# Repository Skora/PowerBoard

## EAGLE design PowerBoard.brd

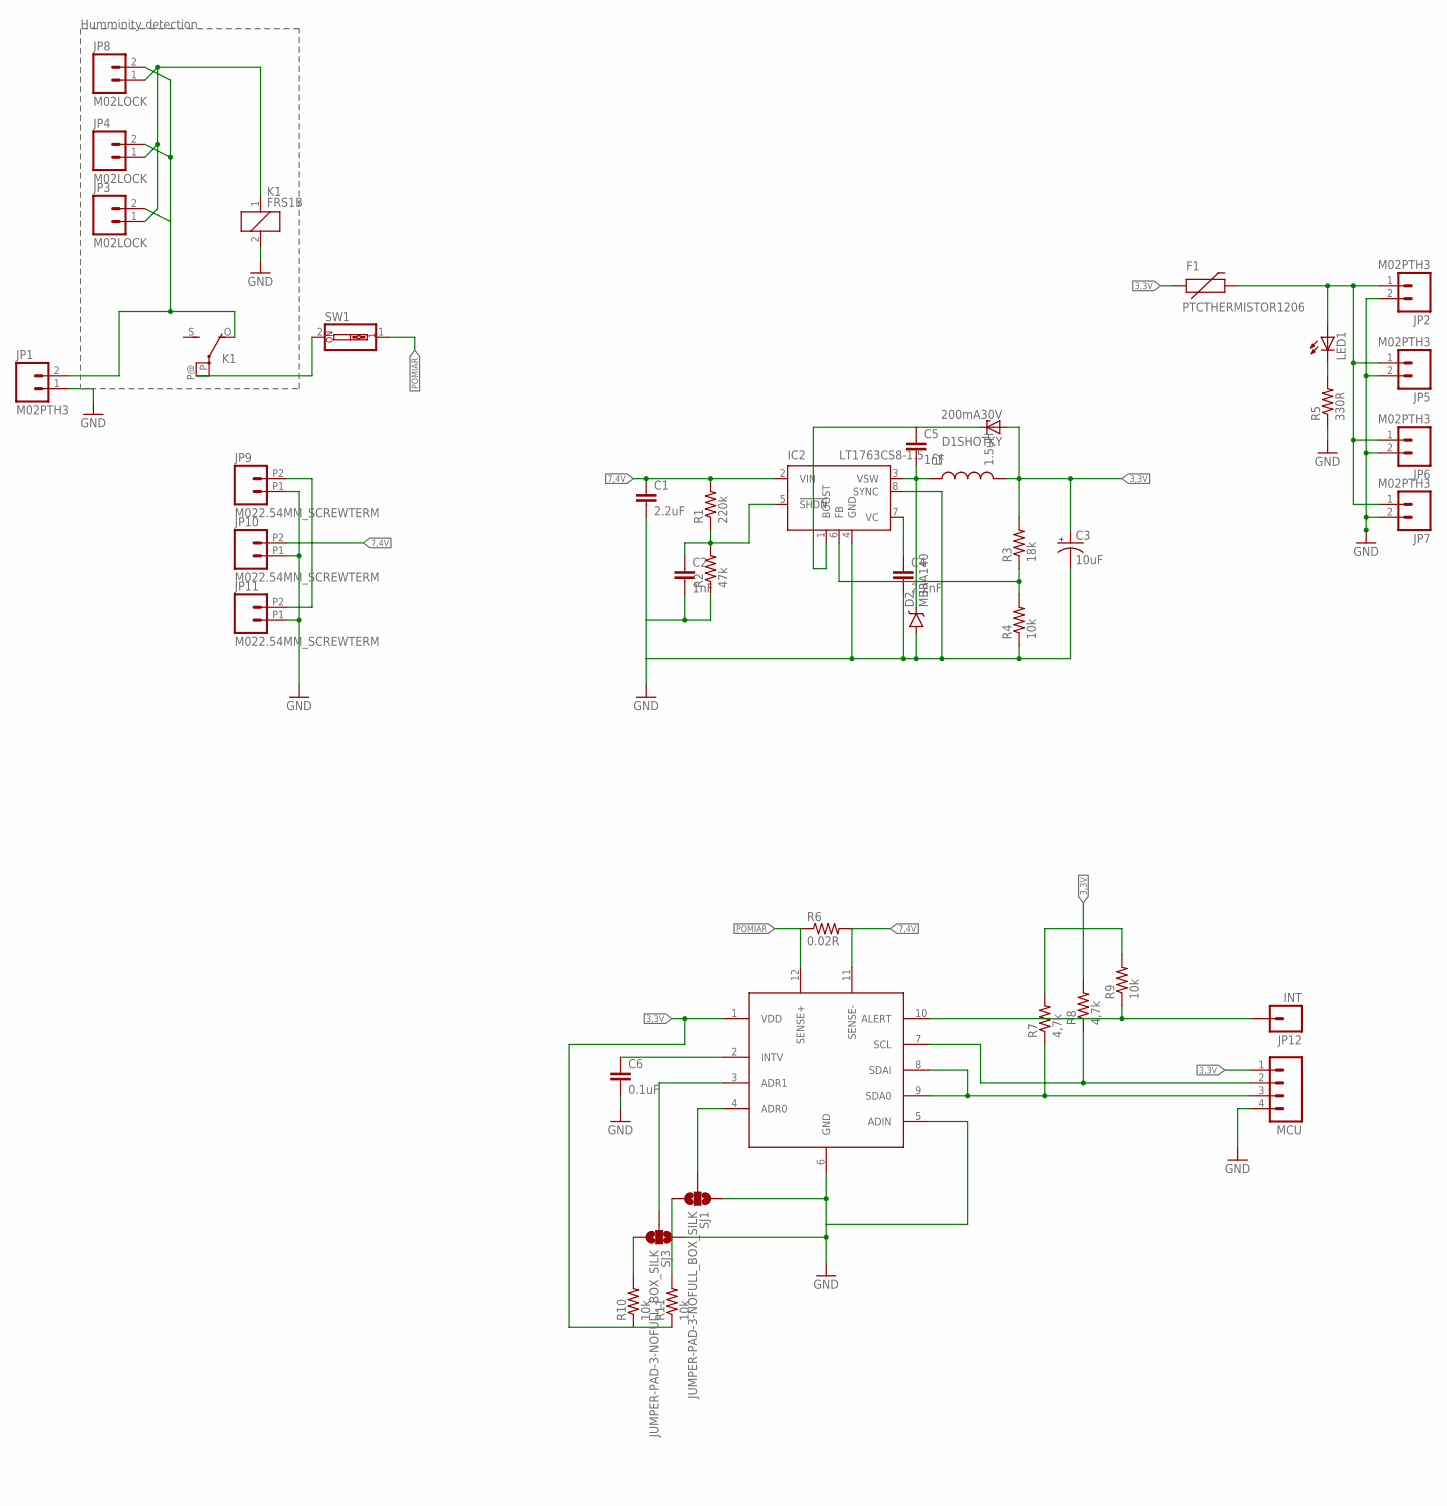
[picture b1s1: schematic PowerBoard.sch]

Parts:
C1: 2.2uF; 0805
C2, C5: 1nF; 0805
C3: 10uF; PANASONIC_C
C4: 2.2nF; 0805
C6: 0.1uF; 0805
D1SHOTKY: 200mA30V; SOD80C
D2: MBRA140; SMA-DIODE
F1: PTCTHERMISTOR1206; PTC-1206
IC2: LT1763CS8-1.5; SOIC8
JP1, JP2, JP5, JP6, JP7: M02PTH3; 1X02_LONGPADS
JP3, JP4, JP8: M02LOCK; 1X02_LOCK
JP9, JP10, JP11: M022.54MM_SCREWTERM; 1X02_2.54_SCREWTERM
JP12: INT; 1X01_LONGPAD
K1: FRS1B
L2: 1.5uH; B82462G
LED1: LEDSML0805; SML0805
MCU: M04POLAR_LOCK; MOLEX-1X4_LOCK
R1: 220k; 0805
R2: 47k; 0805
R3: 18k; 0805
R4, R9, R10, R11: 10k; 0805
R5: 330R; 0805
R6: 0.02R; R2512
R7, R8: 4,7k; 0805
SJ1, SJ3: JUMPER-PAD-3-NOFULL_BOX_SILK; PAD-JUMPER-3-NO_YES_SILK_FULL_BOX
SW1: SW_DIP-1; EDG-01
U$1: LTC2945; SOP65P490X110-12N

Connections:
3,3V: C3.+, D1SHOTKY.A, F1.1, L2.P$2 (2), MCU.1, R3.2, R7.2, R8.2, R9.2, R10.1, R11.1, U$1.1 (VDD)
7,4V: C1.1, IC2.2 (VIN), JP9.P2 (2), JP10.P2 (2), JP11.P2 (2), R1.2, R6.2, U$1.11 (SENSE-)
AFERFUSE: F1.2, JP2.1, JP5.1, JP6.1, JP7.1, LED1.A
COIL: JP3.1, JP4.1, JP8.1, K1.1
COUT: C5.2, D2.C, IC2.3 (VSW), L2.P$1 (1)
GND: C1.2, C2.2, C3.-, C4.2, C6.2, D2.A, IC2.4 (GND), IC2.8 (SYNC), JP1.1, JP2.2, JP5.2, JP6.2, JP7.2, JP9.P1 (1), JP10.P1 (1), JP11.P1 (1), K1.2, MCU.4, R2.1, R4.1, R5.1, SJ1.1, SJ3.1, U$1.5 (ADIN), U$1.6 (GND)
unnamed: C2.1, IC2.5 (!SHDN), R1.1, R2.2
unnamed: IC2.6 (FB), R3.1, R4.2
unnamed: C4.1, IC2.7 (VC)
unnamed: C5.1, D1SHOTKY.C, IC2.1 (BOOST)
unnamed: LED1.C, R5.2
unnamed: JP12.1, R9.1, U$1.10 (ALERT)
unnamed: MCU.2, R8.1, U$1.7 (SCL)
unnamed: MCU.3, R7.1, U$1.8 (SDAI), U$1.9 (SDA0)
unnamed: C6.1, U$1.2 (INTV)
unnamed: SJ3.2, U$1.3 (ADR1)
unnamed: SJ1.2, U$1.4 (ADR0)
unnamed: R10.2, SJ3.3
unnamed: R11.2, SJ1.3
POMIAR: R6.1, SW1.1, U$1.12 (SENSE+)
PRERELAY: JP1.2, JP3.2, JP4.2, JP8.2, K1.O
PRESWITCH: K1.P, K1.P@, SW1.2

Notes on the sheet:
Humminity detection

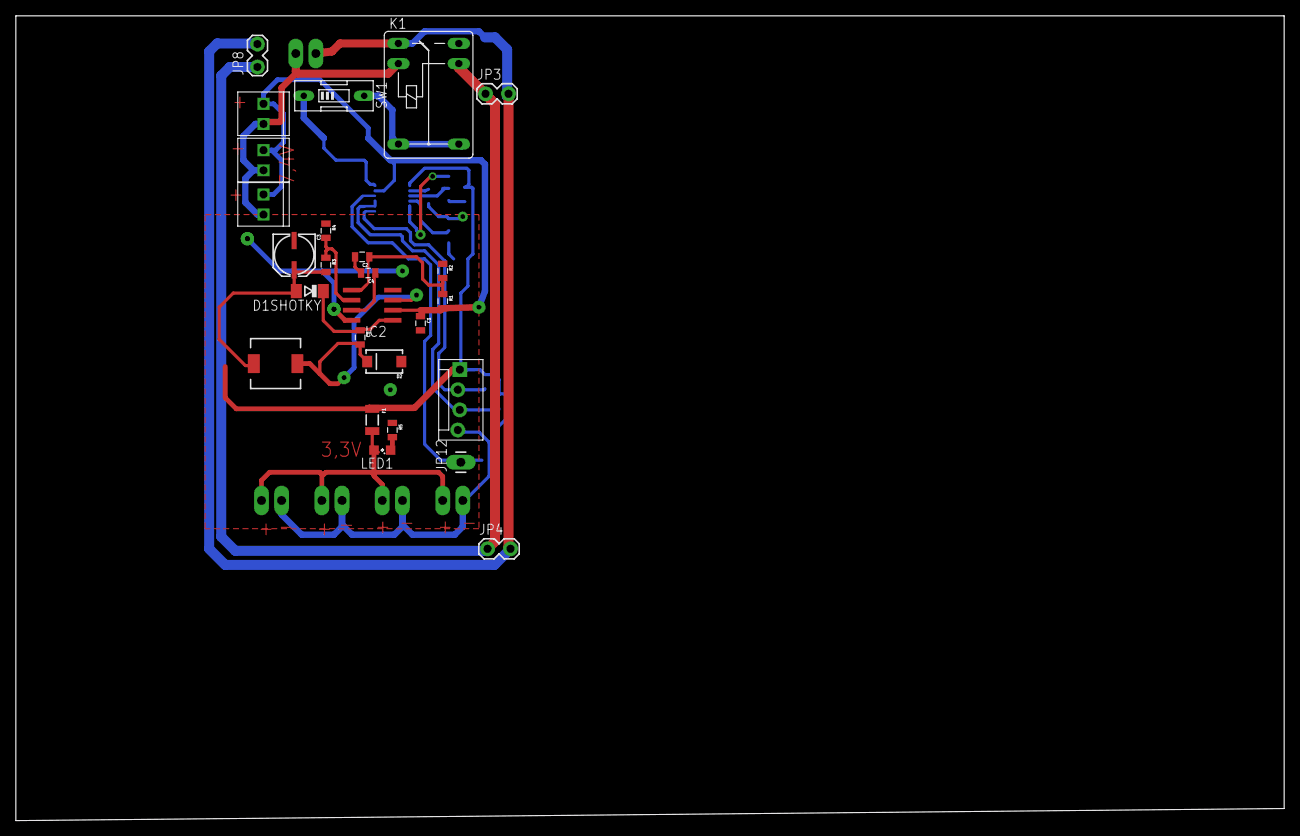
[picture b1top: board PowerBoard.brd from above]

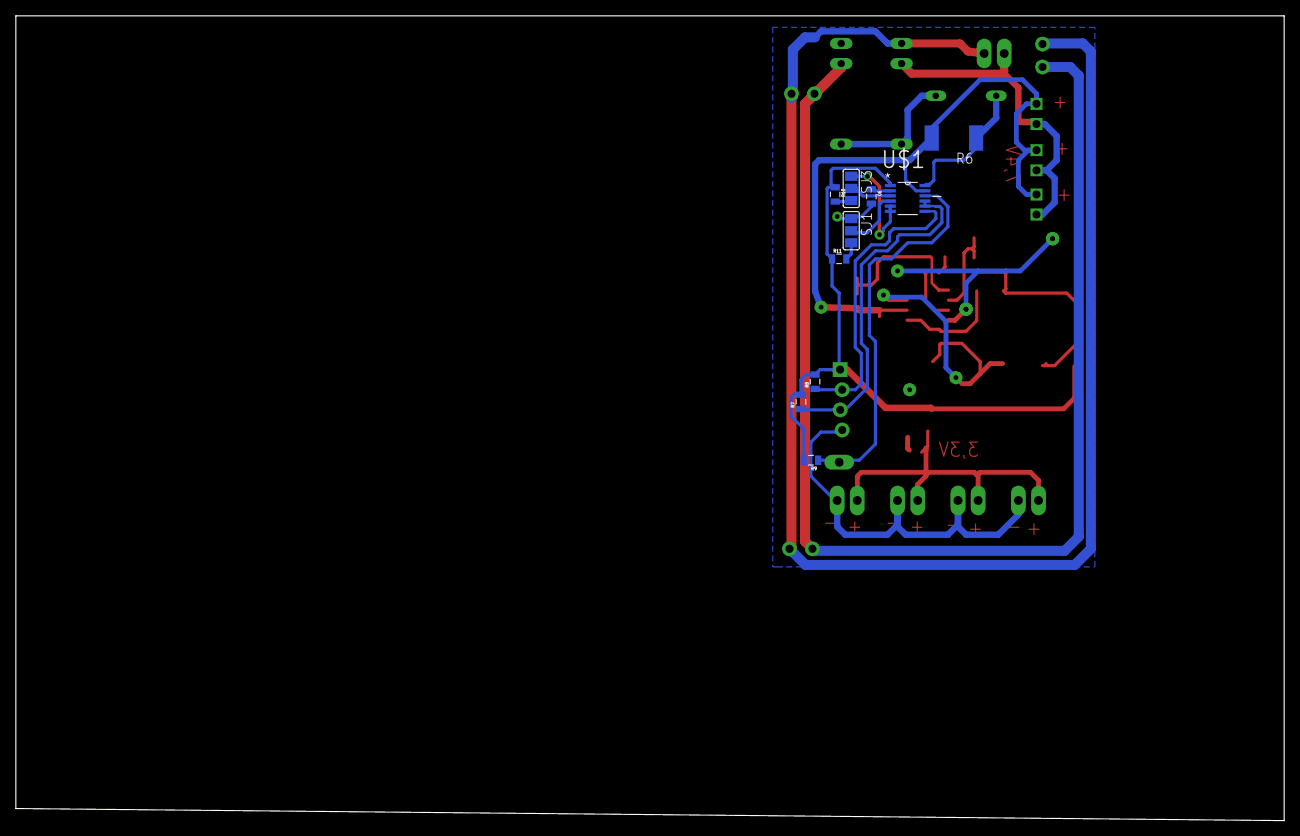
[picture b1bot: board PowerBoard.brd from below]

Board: 2 copper layers, 160.0 x 101.5 mm, 41 parts (10 on the bottom side), 22 nets.

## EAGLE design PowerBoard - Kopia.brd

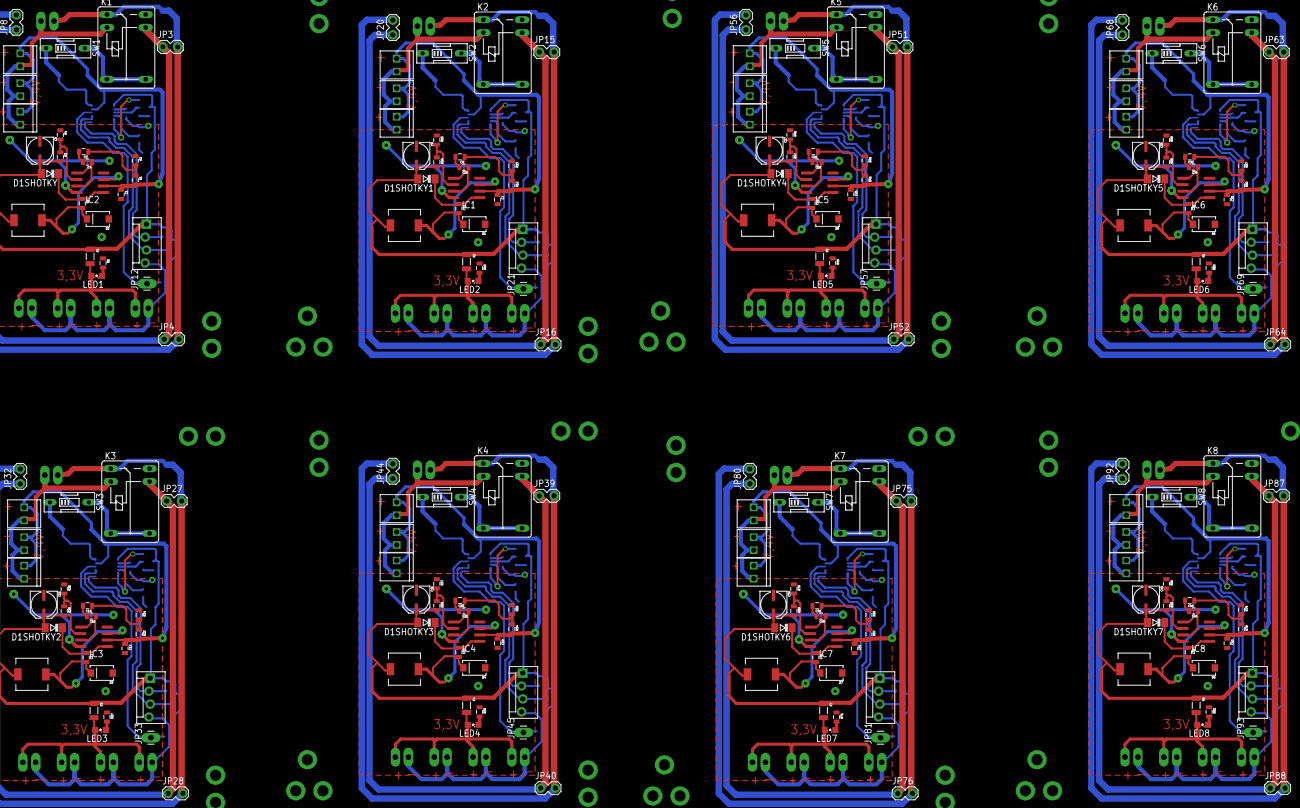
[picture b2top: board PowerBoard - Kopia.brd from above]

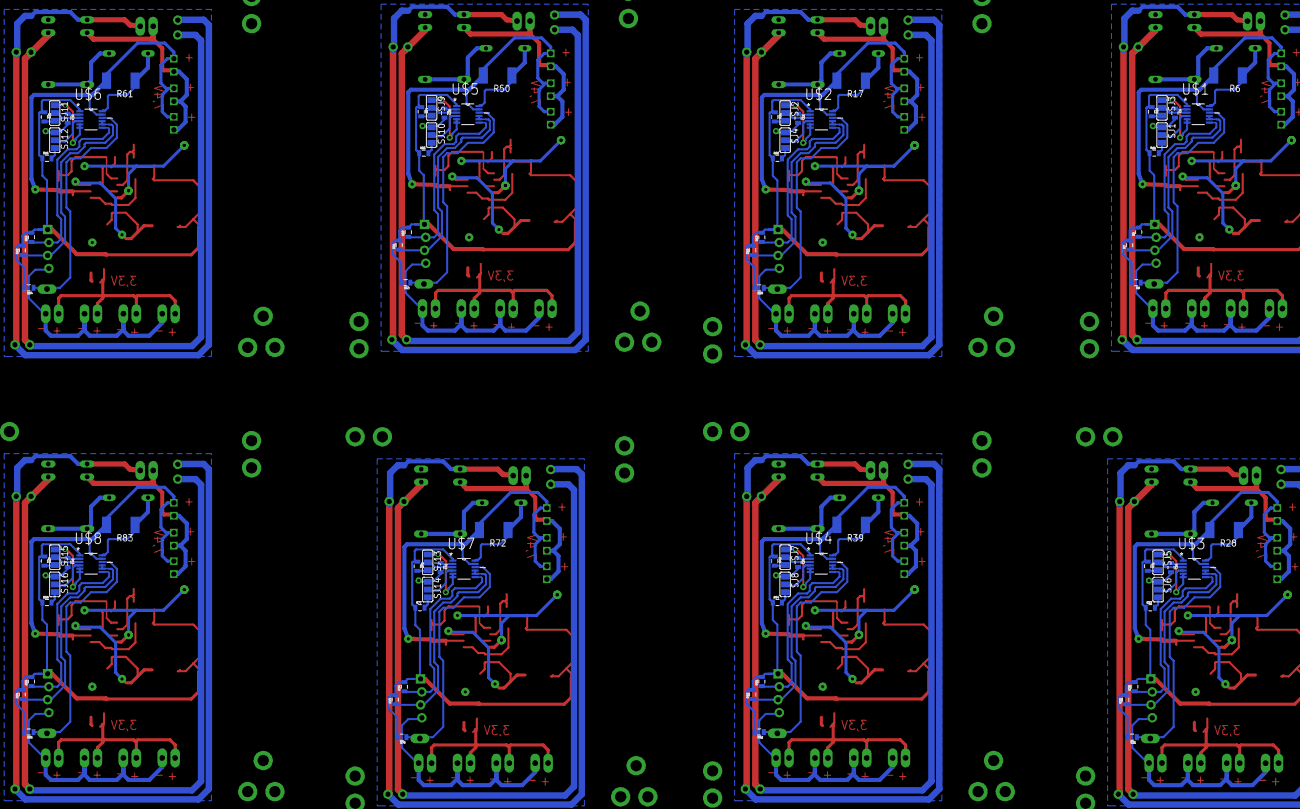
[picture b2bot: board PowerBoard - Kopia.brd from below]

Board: 2 copper layers, 328 parts (80 on the bottom side), 176 nets.

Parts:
C1, C7, C13, C19, C25, C31, C37, C43: 2.2uF; 0805
C2, C5, C8, C11, C14, C17, C20, C23, C26, C29, C32, C35, C38, C41, C44, C47: 1nF; 0805
C3, C9, C15, C21, C27, C33, C39, C45: 10uF; PANASONIC_C
C4, C10, C16, C22, C28, C34, C40, C46: 2.2nF; 0805
C6, C12, C18, C24, C30, C36, C42, C48: 0.1uF; 0805
D1, D2, D3, D4, D5, D6, D7, D8: MBRA140; SMA-DIODE
D1SHOTKY, D1SHOTKY1, D1SHOTKY2, D1SHOTKY3, D1SHOTKY4, D1SHOTKY5, D1SHOTKY6, D1SHOTKY7: 200mA30V; SOD80C
F1, F2, F3, F4, F5, F6, F7, F8: PTCTHERMISTOR1206; PTC-1206
IC1, IC2, IC3, IC4, IC5, IC6, IC7, IC8: LT1763CS8-1.5; SOIC8
JP1, JP2, JP5, JP6, JP7, JP13, JP14, JP17, JP18, JP19, JP25, JP26, JP29, JP30, JP31, JP37, JP38, JP41, JP42, JP43, JP49, JP50, JP53, JP54, JP55, JP61, JP62, JP65, JP66, JP67, JP73, JP74, JP77, JP78, JP79, JP85, JP86, JP89, JP90, JP91: M02PTH3; 1X02_LONGPADS
JP3, JP4, JP8, JP15, JP16, JP20, JP27, JP28, JP32, JP39, JP40, JP44, JP51, JP52, JP56, JP63, JP64, JP68, JP75, JP76, JP80, JP87, JP88, JP92: M02LOCK; 1X02_LOCK
JP9, JP10, JP11, JP22, JP23, JP24, JP34, JP35, JP36, JP46, JP47, JP48, JP58, JP59, JP60, JP70, JP71, JP72, JP82, JP83, JP84, JP94, JP95, JP96: M022.54MM_SCREWTERM; 1X02_2.54_SCREWTERM
JP12, JP21, JP33, JP45, JP57, JP69, JP81, JP93: INT; 1X01_LONGPAD
K1, K2, K3, K4, K5, K6, K7, K8: FRS1B
L1, L2, L3, L4, L5, L6, L7, L8: 1.5uH; B82462G
LED1, LED2, LED3, LED4, LED5, LED6, LED7, LED8: SML0805
MCU, MCU1, MCU2, MCU3, MCU4, MCU5, MCU6, MCU7: MOLEX-1X4_LOCK
R1, R12, R23, R34, R45, R56, R67, R78: 220k; 0805
R2, R13, R24, R35, R46, R57, R68, R79: 47k; 0805
R3, R14, R25, R36, R47, R58, R69, R80: 18k; 0805
R4, R9, R10, R11, R15, R20, R21, R22, R26, R31, R32, R33, R37, R42, R43, R44, R48, R53, R54, R55, R59, R64, R65, R66, R70, R75, R76, R77, R81, R86, R87, R88: 10k; 0805
R5, R16, R27, R38, R49, R60, R71, R82: 330R; 0805
R6, R17, R28, R39, R50, R61, R72, R83: 0.02R; R2512
R7, R8, R18, R19, R29, R30, R40, R41, R51, R52, R62, R63, R73, R74, R84, R85: 4,7k; 0805
SJ1, SJ2, SJ3, SJ4, SJ5, SJ6, SJ7, SJ8, SJ9, SJ10, SJ11, SJ12, SJ13, SJ14, SJ15, SJ16: JUMPER-PAD-3-NOFULL_BOX_SILK; PAD-JUMPER-3-NO_YES_SILK_FULL_BOX
SW1, SW2, SW3, SW4, SW5, SW6, SW7, SW8: EDG-01
U$1, U$2, U$3, U$4, U$5, U$6, U$7, U$8: LTC2945; SOP65P490X110-12N

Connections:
3,3V: C3.+, D1SHOTKY.A, F1.1, L2.P$2, MCU.1, R3.2, R7.2, R8.2, R9.2, R10.1, R11.1, U$1.1
3,3V1: C9.+, D1SHOTKY1.A, F2.1, L1.P$2, MCU1.1, R14.2, R18.2, R19.2, R20.2, R21.1, R22.1, U$2.1
3,3V2: C15.+, D1SHOTKY2.A, F3.1, L3.P$2, MCU2.1, R25.2, R29.2, R30.2, R31.2, R32.1, R33.1, U$3.1
3,3V3: C21.+, D1SHOTKY3.A, F4.1, L4.P$2, MCU3.1, R36.2, R40.2, R41.2, R42.2, R43.1, R44.1, U$4.1
3,3V4: C27.+, D1SHOTKY4.A, F5.1, L5.P$2, MCU4.1, R47.2, R51.2, R52.2, R53.2, R54.1, R55.1, U$5.1
3,3V5: C33.+, D1SHOTKY5.A, F6.1, L6.P$2, MCU5.1, R58.2, R62.2, R63.2, R64.2, R65.1, R66.1, U$6.1
3,3V6: C39.+, D1SHOTKY6.A, F7.1, L7.P$2, MCU6.1, R69.2, R73.2, R74.2, R75.2, R76.1, R77.1, U$7.1
3,3V7: C45.+, D1SHOTKY7.A, F8.1, L8.P$2, MCU7.1, R80.2, R84.2, R85.2, R86.2, R87.1, R88.1, U$8.1
7,4V: C1.1, IC2.2, JP9.P2, JP10.P2, JP11.P2, R1.2, R6.2, U$1.11
7,4V1: C7.1, IC1.2, JP22.P2, JP23.P2, JP24.P2, R12.2, R17.2, U$2.11
7,4V2: C13.1, IC3.2, JP34.P2, JP35.P2, JP36.P2, R23.2, R28.2, U$3.11
7,4V3: C19.1, IC4.2, JP46.P2, JP47.P2, JP48.P2, R34.2, R39.2, U$4.11
7,4V4: C25.1, IC5.2, JP58.P2, JP59.P2, JP60.P2, R45.2, R50.2, U$5.11
7,4V5: C31.1, IC6.2, JP70.P2, JP71.P2, JP72.P2, R56.2, R61.2, U$6.11
7,4V6: C37.1, IC7.2, JP82.P2, JP83.P2, JP84.P2, R67.2, R72.2, U$7.11
7,4V7: C43.1, IC8.2, JP94.P2, JP95.P2, JP96.P2, R78.2, R83.2, U$8.11
AFERFUSE: F1.2, JP2.1, JP5.1, JP6.1, JP7.1, LED1.A
AFERFUSE1: F2.2, JP14.1, JP17.1, JP18.1, JP19.1, LED2.A
AFERFUSE2: F3.2, JP26.1, JP29.1, JP30.1, JP31.1, LED3.A
AFERFUSE3: F4.2, JP38.1, JP41.1, JP42.1, JP43.1, LED4.A
AFERFUSE4: F5.2, JP50.1, JP53.1, JP54.1, JP55.1, LED5.A
AFERFUSE5: F6.2, JP62.1, JP65.1, JP66.1, JP67.1, LED6.A
AFERFUSE6: F7.2, JP74.1, JP77.1, JP78.1, JP79.1, LED7.A
AFERFUSE7: F8.2, JP86.1, JP89.1, JP90.1, JP91.1, LED8.A
COIL: JP3.1, JP4.1, JP8.1, K1.1
COIL1: JP15.1, JP16.1, JP20.1, K2.1
COIL2: JP27.1, JP28.1, JP32.1, K3.1
COIL3: JP39.1, JP40.1, JP44.1, K4.1
COIL4: JP51.1, JP52.1, JP56.1, K5.1
COIL5: JP63.1, JP64.1, JP68.1, K6.1
COIL6: JP75.1, JP76.1, JP80.1, K7.1
COIL7: JP87.1, JP88.1, JP92.1, K8.1
COUT: C5.2, D2.C, IC2.3, L2.P$1
COUT1: C11.2, D1.C, IC1.3, L1.P$1
COUT2: C17.2, D3.C, IC3.3, L3.P$1
COUT3: C23.2, D4.C, IC4.3, L4.P$1
COUT4: C29.2, D5.C, IC5.3, L5.P$1
COUT5: C35.2, D6.C, IC6.3, L6.P$1
COUT6: C41.2, D7.C, IC7.3, L7.P$1
COUT7: C47.2, D8.C, IC8.3, L8.P$1
GND: C1.2, C2.2, C3.-, C4.2, C6.2, D2.A, IC2.4, IC2.8, JP1.1, JP2.2, JP5.2, JP6.2, JP7.2, JP9.P1, JP10.P1, JP11.P1, K1.2, MCU.4, R2.1, R4.1, R5.1, SJ1.1, SJ3.1, U$1.5, U$1.6
GND1: C7.2, C8.2, C9.-, C10.2, C12.2, D1.A, IC1.4, IC1.8, JP13.1, JP14.2, JP17.2, JP18.2, JP19.2, JP22.P1, JP23.P1, JP24.P1, K2.2, MCU1.4, R13.1, R15.1, R16.1, SJ2.1, SJ4.1, U$2.5, U$2.6
GND2: C13.2, C14.2, C15.-, C16.2, C18.2, D3.A, IC3.4, IC3.8, JP25.1, JP26.2, JP29.2, JP30.2, JP31.2, JP34.P1, JP35.P1, JP36.P1, K3.2, MCU2.4, R24.1, R26.1, R27.1, SJ5.1, SJ6.1, U$3.5, U$3.6
GND3: C19.2, C20.2, C21.-, C22.2, C24.2, D4.A, IC4.4, IC4.8, JP37.1, JP38.2, JP41.2, JP42.2, JP43.2, JP46.P1, JP47.P1, JP48.P1, K4.2, MCU3.4, R35.1, R37.1, R38.1, SJ7.1, SJ8.1, U$4.5, U$4.6
GND4: C25.2, C26.2, C27.-, C28.2, C30.2, D5.A, IC5.4, IC5.8, JP49.1, JP50.2, JP53.2, JP54.2, JP55.2, JP58.P1, JP59.P1, JP60.P1, K5.2, MCU4.4, R46.1, R48.1, R49.1, SJ9.1, SJ10.1, U$5.5, U$5.6
GND5: C31.2, C32.2, C33.-, C34.2, C36.2, D6.A, IC6.4, IC6.8, JP61.1, JP62.2, JP65.2, JP66.2, JP67.2, JP70.P1, JP71.P1, JP72.P1, K6.2, MCU5.4, R57.1, R59.1, R60.1, SJ11.1, SJ12.1, U$6.5, U$6.6
GND6: C37.2, C38.2, C39.-, C40.2, C42.2, D7.A, IC7.4, IC7.8, JP73.1, JP74.2, JP77.2, JP78.2, JP79.2, JP82.P1, JP83.P1, JP84.P1, K7.2, MCU6.4, R68.1, R70.1, R71.1, SJ13.1, SJ14.1, U$7.5, U$7.6
GND7: C43.2, C44.2, C45.-, C46.2, C48.2, D8.A, IC8.4, IC8.8, JP85.1, JP86.2, JP89.2, JP90.2, JP91.2, JP94.P1, JP95.P1, JP96.P1, K8.2, MCU7.4, R79.1, R81.1, R82.1, SJ15.1, SJ16.1, U$8.5, U$8.6
unnamed: C2.1, IC2.5, R1.1, R2.2
unnamed: C8.1, IC1.5, R12.1, R13.2
unnamed: IC2.6, R3.1, R4.2
unnamed: C4.1, IC2.7
unnamed: C5.1, D1SHOTKY.C, IC2.1
unnamed: LED1.C, R5.2
unnamed: JP12.1, R9.1, U$1.10
unnamed: MCU.2, R8.1, U$1.7
unnamed: MCU.3, R7.1, U$1.8, U$1.9
unnamed: C6.1, U$1.2
unnamed: SJ3.2, U$1.3
unnamed: SJ1.2, U$1.4
unnamed: R10.2, SJ3.3
unnamed: R11.2, SJ1.3
unnamed: IC1.6, R14.1, R15.2
unnamed: C10.1, IC1.7
unnamed: C11.1, D1SHOTKY1.C, IC1.1
unnamed: LED2.C, R16.2
unnamed: C12.1, U$2.2
unnamed: MCU1.2, R19.1, U$2.7
unnamed: MCU1.3, R18.1, U$2.8, U$2.9
unnamed: JP21.1, R20.1, U$2.10
unnamed: SJ2.2, U$2.3
unnamed: SJ4.2, U$2.4
unnamed: R21.2, SJ2.3
unnamed: R22.2, SJ4.3
unnamed: C14.1, IC3.5, R23.1, R24.2
unnamed: IC3.6, R25.1, R26.2
unnamed: C16.1, IC3.7
unnamed: C17.1, D1SHOTKY2.C, IC3.1
unnamed: LED3.C, R27.2
unnamed: C18.1, U$3.2
unnamed: MCU2.2, R30.1, U$3.7
unnamed: MCU2.3, R29.1, U$3.8, U$3.9
unnamed: JP33.1, R31.1, U$3.10
unnamed: SJ5.2, U$3.3
unnamed: SJ6.2, U$3.4
unnamed: R32.2, SJ5.3
unnamed: R33.2, SJ6.3
unnamed: C20.1, IC4.5, R34.1, R35.2
unnamed: IC4.6, R36.1, R37.2
unnamed: C22.1, IC4.7
unnamed: C23.1, D1SHOTKY3.C, IC4.1
unnamed: LED4.C, R38.2
unnamed: C24.1, U$4.2
unnamed: MCU3.2, R41.1, U$4.7
unnamed: MCU3.3, R40.1, U$4.8, U$4.9
unnamed: JP45.1, R42.1, U$4.10
unnamed: SJ7.2, U$4.3
unnamed: SJ8.2, U$4.4
unnamed: R43.2, SJ7.3
unnamed: R44.2, SJ8.3
unnamed: C26.1, IC5.5, R45.1, R46.2
unnamed: IC5.6, R47.1, R48.2
unnamed: C28.1, IC5.7
unnamed: C29.1, D1SHOTKY4.C, IC5.1
unnamed: LED5.C, R49.2
unnamed: C30.1, U$5.2
unnamed: MCU4.2, R52.1, U$5.7
unnamed: MCU4.3, R51.1, U$5.8, U$5.9
unnamed: JP57.1, R53.1, U$5.10
unnamed: SJ9.2, U$5.3
unnamed: SJ10.2, U$5.4
unnamed: R54.2, SJ9.3
unnamed: R55.2, SJ10.3
unnamed: C32.1, IC6.5, R56.1, R57.2
unnamed: IC6.6, R58.1, R59.2
unnamed: C34.1, IC6.7
unnamed: C35.1, D1SHOTKY5.C, IC6.1
unnamed: LED6.C, R60.2
unnamed: C36.1, U$6.2
unnamed: MCU5.2, R63.1, U$6.7
unnamed: MCU5.3, R62.1, U$6.8, U$6.9
unnamed: JP69.1, R64.1, U$6.10
unnamed: SJ11.2, U$6.3
unnamed: SJ12.2, U$6.4
unnamed: R65.2, SJ11.3
unnamed: R66.2, SJ12.3
unnamed: C38.1, IC7.5, R67.1, R68.2
unnamed: IC7.6, R69.1, R70.2
unnamed: C40.1, IC7.7
unnamed: C41.1, D1SHOTKY6.C, IC7.1
unnamed: LED7.C, R71.2
unnamed: C42.1, U$7.2
unnamed: MCU6.2, R74.1, U$7.7
unnamed: MCU6.3, R73.1, U$7.8, U$7.9
unnamed: JP81.1, R75.1, U$7.10
unnamed: SJ13.2, U$7.3
unnamed: SJ14.2, U$7.4
unnamed: R76.2, SJ13.3
unnamed: R77.2, SJ14.3
unnamed: C44.1, IC8.5, R78.1, R79.2
unnamed: IC8.6, R80.1, R81.2
unnamed: C46.1, IC8.7
unnamed: C47.1, D1SHOTKY7.C, IC8.1
unnamed: LED8.C, R82.2
unnamed: C48.1, U$8.2
unnamed: MCU7.2, R85.1, U$8.7
unnamed: MCU7.3, R84.1, U$8.8, U$8.9
unnamed: JP93.1, R86.1, U$8.10
unnamed: SJ15.2, U$8.3
unnamed: SJ16.2, U$8.4
unnamed: R87.2, SJ15.3
unnamed: R88.2, SJ16.3
POMIAR: R6.1, SW1.1, U$1.12
POMIAR1: R17.1, SW2.1, U$2.12
POMIAR2: R28.1, SW3.1, U$3.12
POMIAR3: R39.1, SW4.1, U$4.12
POMIAR4: R50.1, SW5.1, U$5.12
POMIAR5: R61.1, SW6.1, U$6.12
POMIAR6: R72.1, SW7.1, U$7.12
POMIAR7: R83.1, SW8.1, U$8.12
PRERELAY: JP1.2, JP3.2, JP4.2, JP8.2, K1.O
PRERELAY1: JP13.2, JP15.2, JP16.2, JP20.2, K2.O
PRERELAY2: JP25.2, JP27.2, JP28.2, JP32.2, K3.O
PRERELAY3: JP37.2, JP39.2, JP40.2, JP44.2, K4.O
PRERELAY4: JP49.2, JP51.2, JP52.2, JP56.2, K5.O
PRERELAY5: JP61.2, JP63.2, JP64.2, JP68.2, K6.O
PRERELAY6: JP73.2, JP75.2, JP76.2, JP80.2, K7.O
PRERELAY7: JP85.2, JP87.2, JP88.2, JP92.2, K8.O
PRESWITCH: K1.P, K1.P@, SW1.2
PRESWITCH1: K2.P, K2.P@, SW2.2
PRESWITCH2: K3.P, K3.P@, SW3.2
PRESWITCH3: K4.P, K4.P@, SW4.2
PRESWITCH4: K5.P, K5.P@, SW5.2
PRESWITCH5: K6.P, K6.P@, SW6.2
PRESWITCH6: K7.P, K7.P@, SW7.2
PRESWITCH7: K8.P, K8.P@, SW8.2

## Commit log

2015-11-24 Power board Version.1

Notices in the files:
parts and their libraries:
SparkFun-Connectors: Licensing: Creative Commons ShareAlike 4.0 International - https://creativecommons.org/licenses/by-sa/4.0
